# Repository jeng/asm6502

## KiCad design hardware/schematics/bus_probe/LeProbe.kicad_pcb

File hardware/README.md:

# Hardware version of the screensaver emulator

## BOM

- 1 x 32x32 RGB LED Matrix Panel - 4mm Pitch[ID:607] 
- 1 x Keyestudio Mega 2560
- 1 x W65C02
- 1 x 28C256 256K Parallel EEPROM
- 1 x 62256 256K SRAM
- 1 x 7400 Quad 2-input NAND Gate
- 2 x 7421 Dual 4-input AND Gate
- 2 x 7408 Quad 2-input AND Gate
- 2 x 7414 Dual Gate/Hex Inverter
- 1 x 7432 Quad 2-input OR Gate
- 11 bypass capacitors

## Memory Map

|low|high|area|
|---|----|----|
|0x0000|0x00FB|RAM|
|0x00FC|0x00FD|Not Used|
|0x00FE|0x00FE|RNG|
|0x00FF|0x00FF|ASCII Code of the last key press|
|0x0100|0x0199|RAM|
|0x0200|0x05FF|Framebuffer|
|0x05FF|0x7FFF|RAM|
|0x8000|0xFFFF|ROM|

## Disclaimer

I'm doing this as a hobby.  I make no guarantees about the safety or the
correctness of what is provided.  It is provided "as is" without express or 
implied warranty.

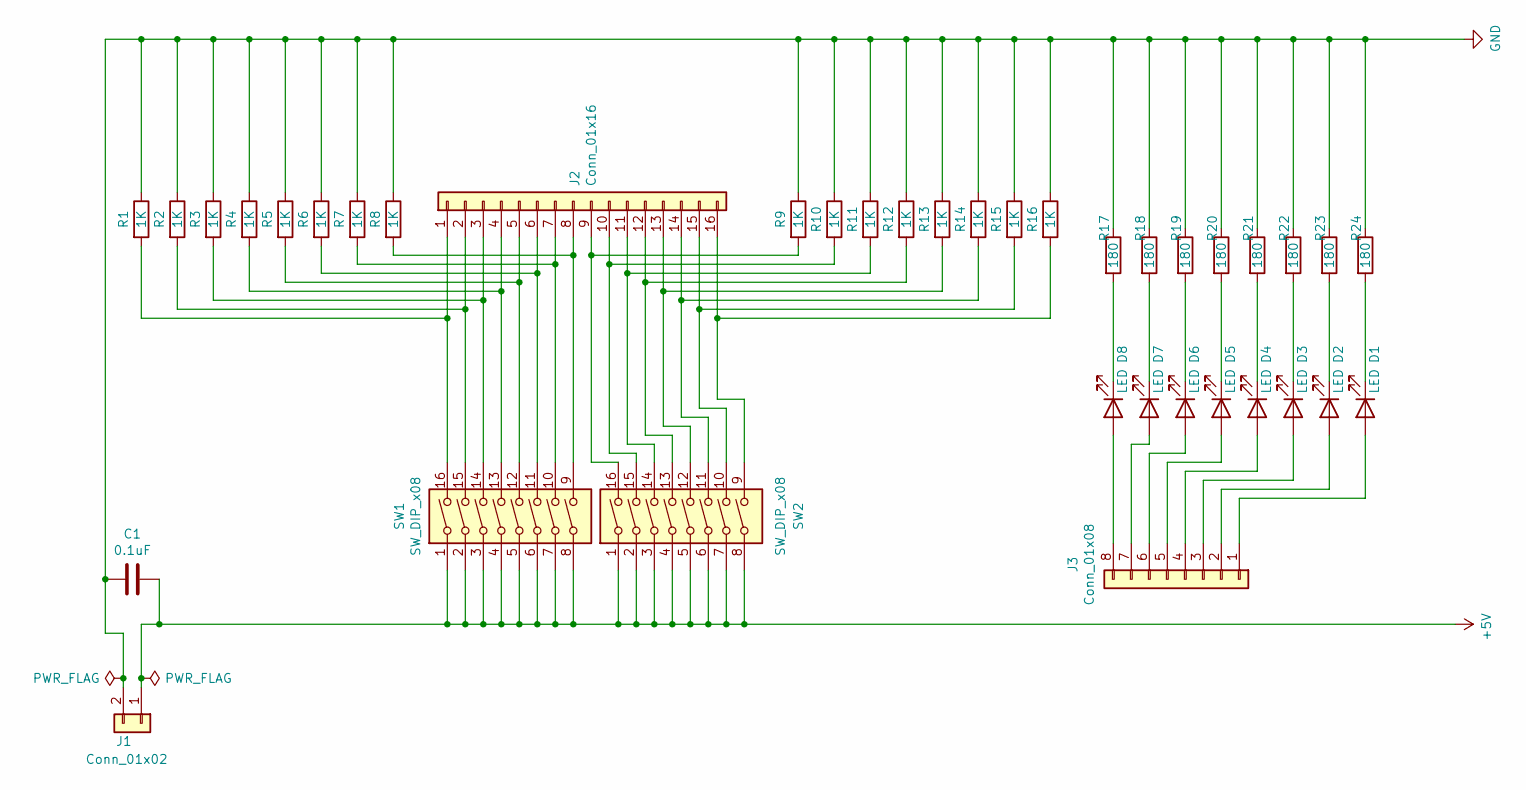
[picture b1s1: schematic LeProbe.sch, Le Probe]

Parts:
C1: 0.1uF; C_Disc_D3.8mm_W2.6mm_P2.50mm
D1, D2, D3, D4, D5, D6, D7, D8: LED; LED_D5.0mm
J1: Conn_01x02; PinHeader_1x02_P2.54mm_Vertical
J2: Conn_01x16; PinHeader_1x16_P2.54mm_Vertical
J3: Conn_01x08; PinHeader_1x08_P2.54mm_Vertical
R1, R2, R3, R4, R5, R6, R7, R8, R9, R10, R11, R12, R13, R14, R15, R16: 1K; R_Axial_DIN0204_L3.6mm_D1.6mm_P7.62mm_Horizontal
R17, R18, R19, R20, R21, R22, R23, R24: 180; R_Axial_DIN0204_L3.6mm_D1.6mm_P7.62mm_Horizontal
SW1, SW2: SW_DIP_x08; SW_DIP_SPSTx08_Slide_9.78x22.5mm_W7.62mm_P2.54mm

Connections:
+5V: C1.2, J1.1, SW1.1, SW1.2, SW1.3, SW1.4, SW1.5, SW1.6, SW1.7, SW1.8, SW2.1, SW2.2, SW2.3, SW2.4, SW2.5, SW2.6, SW2.7, SW2.8
GND: C1.1, J1.2, R1.1, R2.1, R3.1, R4.1, R5.1, R6.1, R7.1, R8.1, R9.1, R10.1, R11.1, R12.1, R13.1, R14.1, R15.1, R16.1, R17.1, R18.1, R19.1, R20.1, R21.1, R22.1, R23.1, R24.1
unnamed: D1.1 (K), R24.2
unnamed: D1.2 (A), J3.1
unnamed: D2.1 (K), R23.2
unnamed: D2.2 (A), J3.2
unnamed: D3.1 (K), R22.2
unnamed: D3.2 (A), J3.3
unnamed: D4.1 (K), R21.2
unnamed: D4.2 (A), J3.4
unnamed: D5.1 (K), R20.2
unnamed: D5.2 (A), J3.5
unnamed: D6.1 (K), R19.2
unnamed: D6.2 (A), J3.6
unnamed: D7.1 (K), R18.2
unnamed: D7.2 (A), J3.7
unnamed: D8.1 (K), R17.2
unnamed: D8.2 (A), J3.8
unnamed: J2.1, R1.2, SW1.16
unnamed: J2.2, R2.2, SW1.15
unnamed: J2.3, R3.2, SW1.14
unnamed: J2.4, R4.2, SW1.13
unnamed: J2.5, R5.2, SW1.12
unnamed: J2.6, R6.2, SW1.11
unnamed: J2.7, R7.2, SW1.10
unnamed: J2.8, R8.2, SW1.9
unnamed: J2.9, R9.2, SW2.16
unnamed: J2.10, R10.2, SW2.15
unnamed: J2.11, R11.2, SW2.14
unnamed: J2.12, R12.2, SW2.13
unnamed: J2.13, R13.2, SW2.12
unnamed: J2.14, R14.2, SW2.11
unnamed: J2.15, R15.2, SW2.10
unnamed: J2.16, R16.2, SW2.9

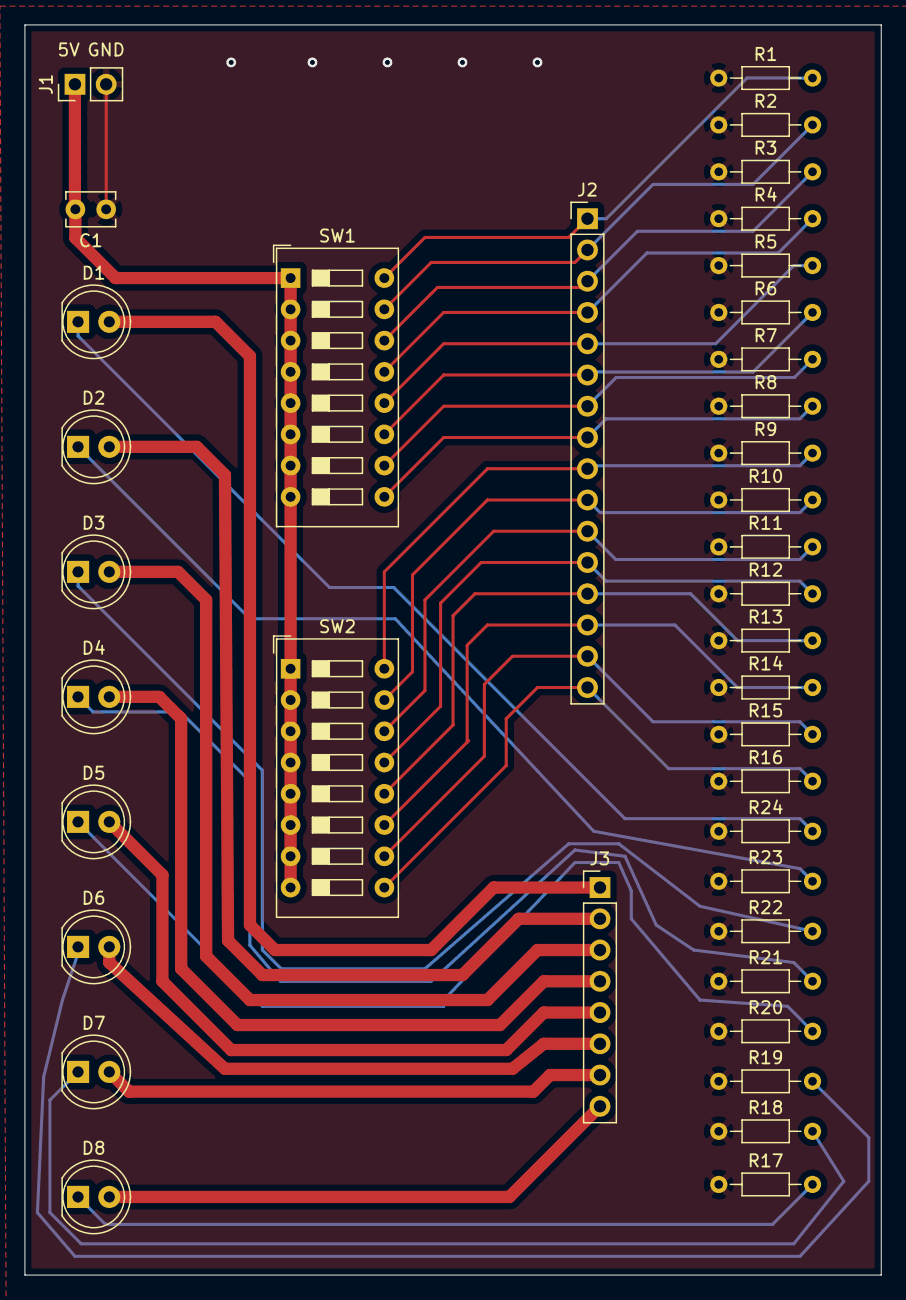
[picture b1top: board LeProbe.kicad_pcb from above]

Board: 2 copper layers, 69.6 x 101.6 mm, 38 parts (0 on the bottom side), 34 nets.

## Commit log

2007-04-17 A port, to c, of the javascript 6502 assembler and emulator.
2007-04-17 Added the tokenizer. This moves all of the code, that works on the source file, into one location.
2007-04-17 We can now load a source file and index the labels.
2007-04-17 Started to add the machine code and memory management routines.
2007-04-18 Started to add the parser for parameters.
2007-04-19 Just about have the assembler finished.
2007-04-20 Cool, The assembler seems to be working! My hexdump matches the target hexdump off of the website.
2007-04-20 Added some more test cases.
2007-04-20 The output for the assembler matches all of the output on the website. I'm not real happy with the parser it could use some work. Write now it will break if extra spaces are in the parameter. I could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
2007-04-23 Two important lessons I learned here. The one I should have known is, don't prototype in C. The other one is, table driven parsing is not as elegenant as recursion.
    That leaves me rewritting the tolkenizer, which I don't really need,
    and the parameter parser.
2007-04-23 The parser is rewritten. The new structure is going to make it easier to maintain and generate the machine code.
2007-04-24 Most of the clean up is done. I just need to test a few things.
2007-04-24 The test passed. The hexdumps match the ones from the website.
2007-04-24 Started to port the emulator code.
2007-04-26 Added the jump table, stubs for all of the jump functions, and the address mode fetch function.
2007-04-27 Completed some of the opcode stubs, added a trace routine, changed the way regP was handled, and created test.asm to test the emulator.
2007-05-01 All of the opcodes except add and substract are implemented. The trace function has been inhanced.
    I would like to break the trace out into a seperate debugger.
    I'm going to add ascii output for now so I can test the graphics.
2007-05-04 Text mode emulator is working.
2007-05-04 Stating optimizing by adding the opcode index cache.
2007-05-04 Caching the opcode indexes cut the runtime of opindex down from 60% to 4%.
2007-05-06 Removed execute bit.
2007-05-06 Started to work on the interface.
2007-05-06 Ascii code is in it's own file. Interface is working.
2007-05-08 Fixed an off by one bug in jmpDEC and jmpINC.
2007-05-10 Added next eval to the text mode version. Removed some debugging code from asm6502.c
2007-05-10 Added error checking for assembler parameters.
2007-07-22 Included the screensaver m6502, changed pong.asm and spacer.asm so that they would work without user interaction.
2007-07-22 Added somemore 6502 demos.
2007-07-22 Changed the screensaver so that it would pull the assembly files out of the image/m6502 directory. Added a function to the assembler so that it will take a string as code. The same demo can not run c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
2007-08-04 Added the debugger to the archive. The assembler will now let you disassemble the program that is loaded in memory.
2007-08-04 Fixed the debugger section of the makefile so that it can be compiled away from the xscreensaver code.
2007-08-19 Fixed a bug in the decimal mode subtraction (opcode sbc).
2007-09-10 Fixed the indirect X addressing mode. Before it acted the same as indirect Y.
2007-12-08 Made a change to pong.asm. Not sure what it was :(
2007-12-08 This script creates a header file out of all of the asm files. The screensaver then includes the header file. This makes it easier to add new asm files to the distribution.
2007-12-10 Added the defaultCodePC in preperation for implementing the entry points. pushByte changed and this effected more of the program then I thought it would. The labels use pushByte to calculate their ad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
2007-12-24 Cleaned up the directory by creating a src and asm subdirectories. Added configure.ac and Makfile.am so that I could use the GNU autotools to build the debugger.
2007-12-24 Moved the man file and added a rule to automake to install and distribute the man page.
2007-12-29 Fixed a bug in the immediate greater than code. A divide by FF is not the same as a right shift by one byte. Also wrote the first version of the 6502 wave.
2008-01-03 Completed the wave6502 demo.
2008-01-09 I made some changes to the make file.
2008-01-13 Added the entry point instruction "*=". It allows you to load code at any location in memory.
2008-01-13 I bumped the version number of the debugger, deleted the duplicate assembly fileand added a copywrite statement to the dcb dumper.
2008-01-13 I changed which asm files get included in the distribution.
2008-01-13 Added a script file to help me manage the xscreensaver releases.
2008-01-19 Commit added to the screensaver distribution script.
2008-02-01 JWZ sent in a change that will strip the comments out of the header file.
2008-10-17 I added some new assembly files I found on 6502asm.com.
    The colors.asm has a bug in it. It looks like it tries to read bytes
    past the dcb table.
    For some reason starfield2d doesn't work the same on the
    screensaver. The stars are flying past way to fast.
2008-10-18 I fixed a bug that would cause branches after the *= command to branch to the wrong location. Also, fixed colors.asm so that it doesn't crash.
2008-10-18 Added the screensaver configuration file and manpage.
    Added a script that will run all asm files in a directory for 30
    seconds a piece.
    Made a minor change to colors.asm, the load address should have been
    $700 instead of $7000. We want to just be out of reach of the frame
    buffer which ends a $600
2008-11-22 Author: Jeremy English <jeremy.english@gmail.com> --- log message follows this line ---
    Added a delay to the start field program. I should probable figure out
    a way to throttle the instructions. That way the assembly programs
    could run at a true, blazing fast, 1MHz.
2008-11-22 Added the amiga emulator found on the forum.
2008-12-02 I forgot to add that the header file hand been changed in the screensaver directory.
2008-12-02 Added a snowflake generating assembly program.
2008-12-04 I got rid of the extra loop for the lifecycle.
2009-05-24 Added a fire demo. It is really slow at the moment. It makes one pass through the frame buffer, makes changes to an offscreen buffer and then repaints the entire frame buffer. I need to figure out a 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
2021-05-13 Added some features to the command line emulator
2021-05-13 Added the markdown extension
2021-05-13 Fixed a typo
2022-09-24 Added plotting for vt colors
2022-09-24 Initial upload for the hardware prototype
    Nothing here is close to being finalized. I have it running on a
    breadboard with some successful output. I still need to make the
    schematic, order the pcbs and finalize the firmware.
    I wanted to upload it now so I don't lose track even though I'm not
    crazy about having this stuff public since it is all hacky at the
    moment.
2022-09-25 I added a new address logic simulation
    I also uploaded the schematics for the very simple bus probe.
2022-09-25 updated hardware readme
2022-09-25 I added the bus probe photo.
2022-10-01 I started on the schematics
2022-10-01 I added the initial versions on the cpu and memory card
2022-10-04 I started working on the PCBs
2022-10-06 I ordered the PCB from jlcpcb
2022-10-08 I added pdf files of the schematics
